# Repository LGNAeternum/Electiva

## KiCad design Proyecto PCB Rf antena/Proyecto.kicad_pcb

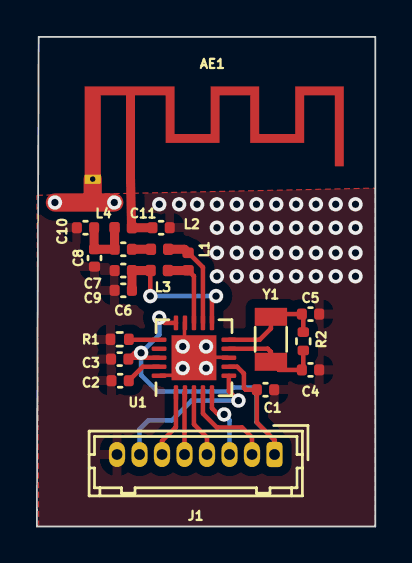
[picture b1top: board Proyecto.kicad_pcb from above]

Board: 2 copper layers, 18.8 x 27.2 mm, 21 parts (0 on the bottom side), 18 nets.

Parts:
AE1: Antenna; Texas_SWRA117D_2.4GHz_Right
C1: 10n; C_0402_1005Metric
C2: 33n; C_0402_1005Metric
C3: 1n; C_0402_1005Metric
C4, C5: 22p; C_0402_1005Metric
C6, C9: C_Small; C_0402_1005Metric
C7: 1p5; C_0402_1005Metric
C8: 1p; C_0402_1005Metric
C10, C11: Cx; C_0402_1005Metric
J1: Conn_01x08_Pin; Hirose_DF13-08P-1.25DSA_1x08_P1.25mm_Vertical
L1: 8n1; L_0402_1005Metric
L2, L4: 3n9; L_0402_1005Metric
L3: 2n7; L_0402_1005Metric
R1: 22K; R_0402_1005Metric
R2: 10M; R_0402_1005Metric
U1: nRF24L01P; QFN-20-1EP_4x4mm_P0.5mm_EP2.5x2.5mm
Y1: 16MHz; Crystal_SMD_3215-2Pin_3.2x1.5mm

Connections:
GND: C1.2, C2.2, C3.2, C4.2, C5.2, C6.2, C8.2, C9.2, C10.2, C11.2, J1.8, R1.2, U1.8 (VSS), U1.14 (VSS), U1.17 (VSS), U1.20 (VSS)
unnamed: AE1.1 (A), C11.1, L4.2
unnamed: C7.1, L2.2
unnamed: C7.2, C8.1, C10.1, L4.1
unnamed: J1.2, U1.4 (MOSI)
unnamed: J1.3, U1.5 (MISO)
unnamed: J1.4, U1.3 (SCK)
unnamed: J1.5, U1.2 (CSN)
unnamed: J1.6, U1.1 (CE)
unnamed: J1.7, U1.6 (IRQ)
unnamed: L1.1, L2.1, U1.12 (ANT1)
unnamed: L1.2, L3.1, U1.13 (ANT2)
unnamed: C2.1, U1.19 (DVDD)
unnamed: R1.1, U1.16 (IREF)
unnamed: C6.1, C9.1, L3.2, U1.11 (VDD_PA)
unnamed: C5.1, R2.2, U1.10 (XC1), Y1.2
unnamed: C4.1, R2.1, U1.9 (XC2), Y1.1
VDD: C1.1, C3.1, J1.1, U1.7 (VDD), U1.15 (VDD), U1.18 (VDD)
